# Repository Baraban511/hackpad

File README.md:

# baraboard
### A complete board designed by me for me with help of many !

# BOM:

    [ ] 1x PCB
    [ ] 12x Cherry MX switches
    [ ] 1x EC11 Encoder
    [ ] 12x WS2812B LEDs

### If possible, I would like the plate in acrylic and the pcb and the case in black. If it's not possible, feel free to choose the best option.

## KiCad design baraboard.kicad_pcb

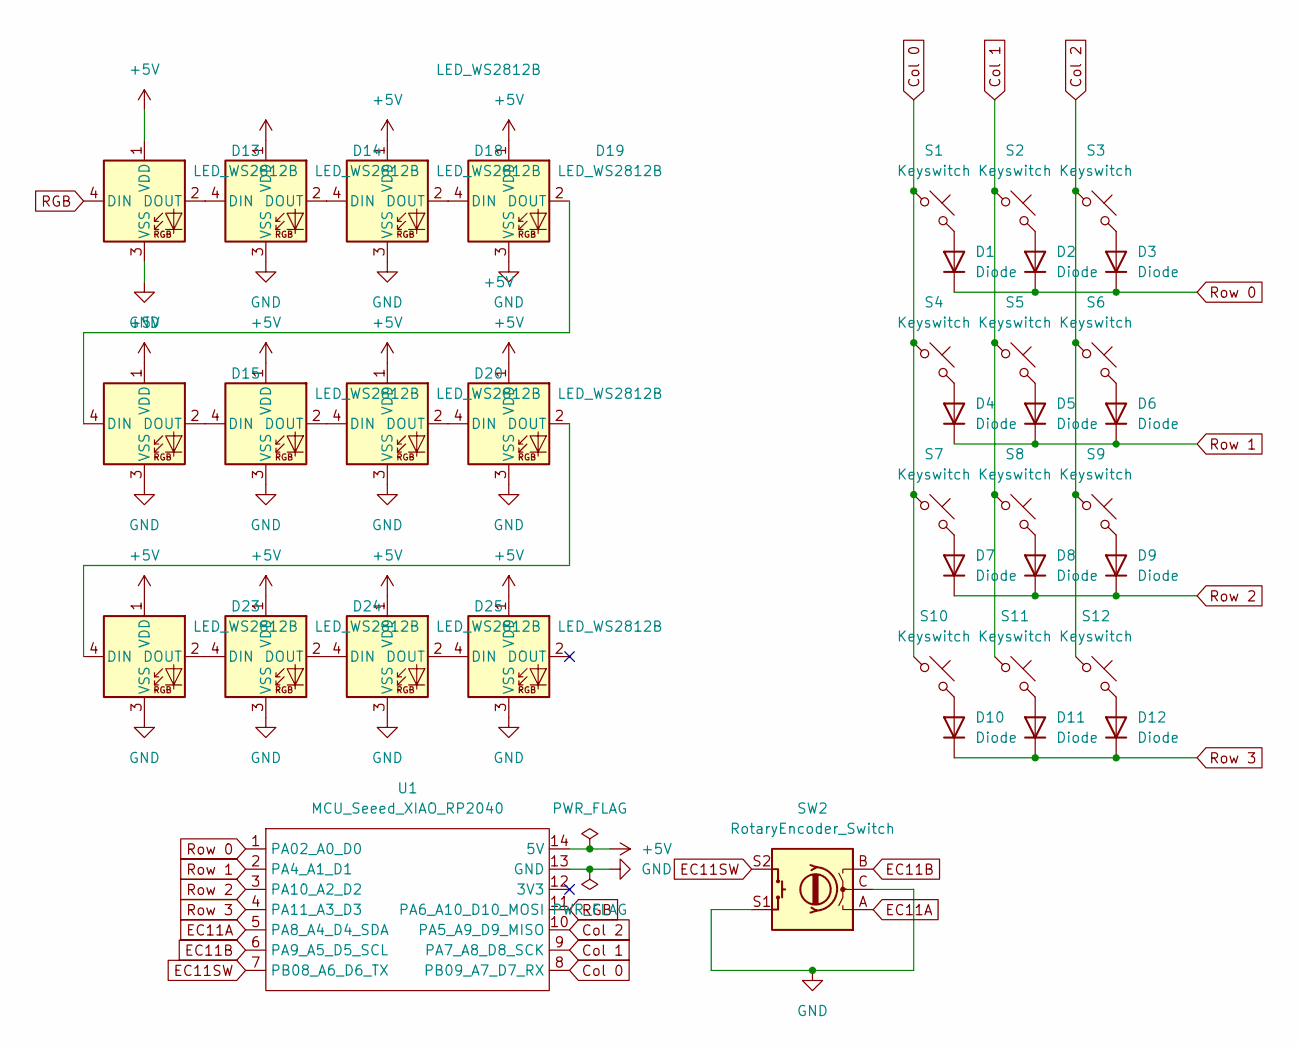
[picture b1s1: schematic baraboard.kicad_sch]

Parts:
D1, D2, D3, D4, D5, D6, D7, D8, D9, D10, D11, D12: Diode; Diode_DO-35
D13, D14, D15, D16, D18, D19, D20, D21, D23, D24, D25, D26: LED_WS2812B; LED_SK6812MINI
S1, S2, S3, S4, S5, S6, S7, S8, S9, S10, S12: Keyswitch; Hotswap_MX_Plated_1.00u
S11: Keyswitch; Hotswap_MX_Plated_2.00u
SW2: RotaryEncoder_Switch; RotaryEncoder_Alps_EC11E-Switch_Vertical_H20mm
U1: MCU_Seeed_XIAO_RP2040; Seeed_XIAO_RP2040

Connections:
+5V: D13.1 (VDD), D14.1 (VDD), D15.1 (VDD), D16.1 (VDD), D18.1 (VDD), D19.1 (VDD), D20.1 (VDD), D21.1 (VDD), D23.1 (VDD), D24.1 (VDD), D25.1 (VDD), D26.1 (VDD), U1.14 (5V)
Col 0: S1.1, S4.1, S7.1, S10.1, U1.8 (PB09_A7_D7_RX)
Col 1: S2.1, S5.1, S8.1, S11.1, U1.9 (PA7_A8_D8_SCK)
Col 2: S3.1, S6.1, S9.1, S12.1, U1.10 (PA5_A9_D9_MISO)
EC11A: SW2.A, U1.5 (PA8_A4_D4_SDA)
EC11B: SW2.B, U1.6 (PA9_A5_D5_SCL)
EC11SW: SW2.S2, U1.7 (PB08_A6_D6_TX)
GND: D13.3 (VSS), D14.3 (VSS), D15.3 (VSS), D16.3 (VSS), D18.3 (VSS), D19.3 (VSS), D20.3 (VSS), D21.3 (VSS), D23.3 (VSS), D24.3 (VSS), D25.3 (VSS), D26.3 (VSS), SW2.C, SW2.S1, U1.13 (GND)
unnamed: D1.2 (A), S1.2
unnamed: D2.2 (A), S2.2
unnamed: D3.2 (A), S3.2
unnamed: D4.2 (A), S4.2
unnamed: D5.2 (A), S5.2
unnamed: D6.2 (A), S6.2
unnamed: D7.2 (A), S7.2
unnamed: D8.2 (A), S8.2
unnamed: D9.2 (A), S9.2
unnamed: D10.2 (A), S10.2
unnamed: D11.2 (A), S11.2
unnamed: D12.2 (A), S12.2
unnamed: D13.2 (DOUT), D14.4 (DIN)
unnamed: D14.2 (DOUT), D15.4 (DIN)
unnamed: D15.2 (DOUT), D19.4 (DIN)
unnamed: D16.4 (DIN), D18.2 (DOUT)
unnamed: D16.2 (DOUT), D20.4 (DIN)
unnamed: D18.4 (DIN), D19.2 (DOUT)
unnamed: D20.2 (DOUT), D21.4 (DIN)
unnamed: D21.2 (DOUT), D23.4 (DIN)
unnamed: D23.2 (DOUT), D24.4 (DIN)
unnamed: D24.2 (DOUT), D25.4 (DIN)
unnamed: D25.2 (DOUT), D26.4 (DIN)
RGB: D13.4 (DIN), U1.11 (PA6_A10_D10_MOSI)
Row 0: D1.1 (K), D2.1 (K), D3.1 (K), U1.1 (PA02_A0_D0)
Row 1: D4.1 (K), D5.1 (K), D6.1 (K), U1.2 (PA4_A1_D1)
Row 2: D7.1 (K), D8.1 (K), D9.1 (K), U1.3 (PA10_A2_D2)
Row 3: D10.1 (K), D11.1 (K), D12.1 (K), U1.4 (PA11_A3_D3)

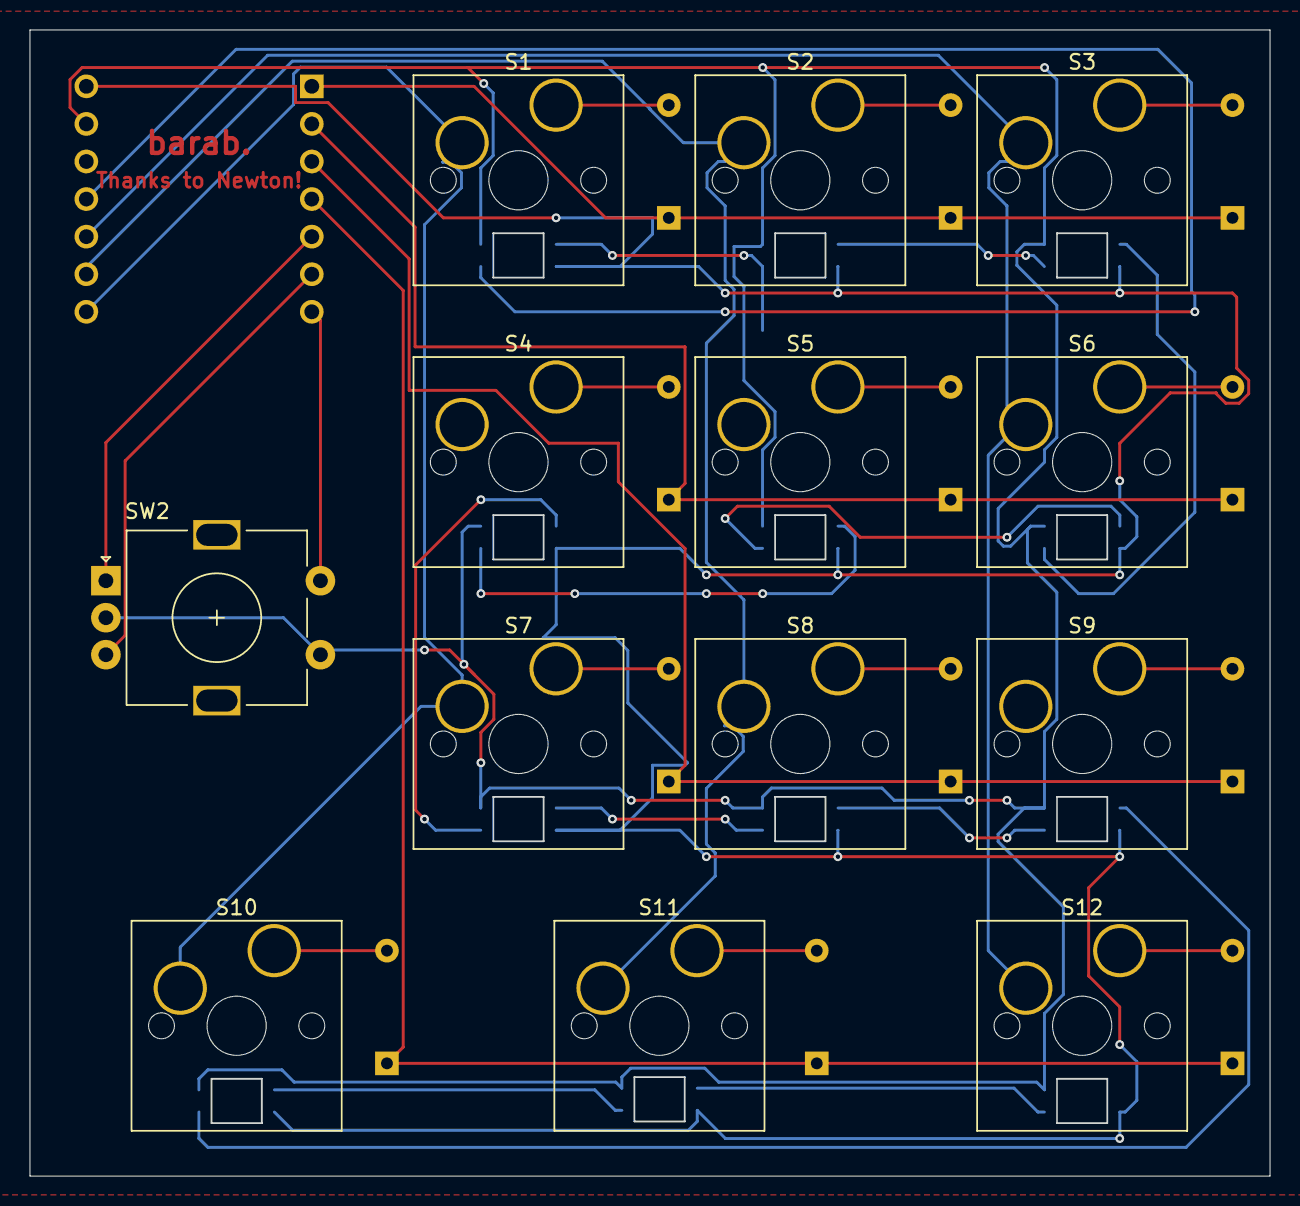
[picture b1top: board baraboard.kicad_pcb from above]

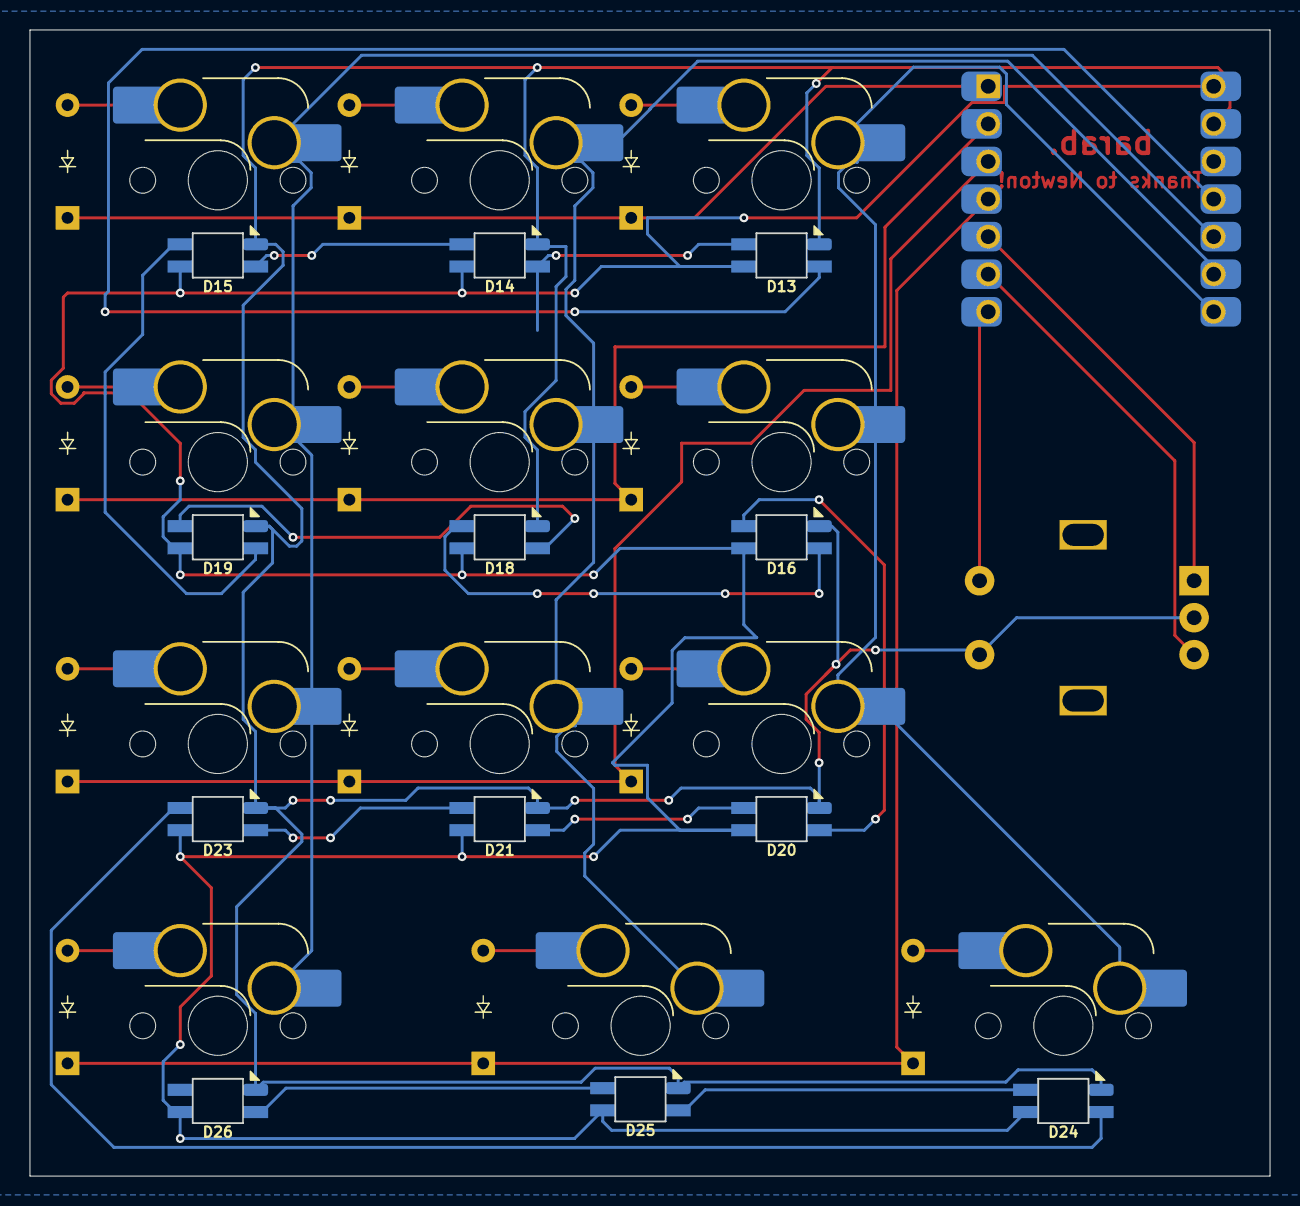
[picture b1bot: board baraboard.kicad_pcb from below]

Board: 2 copper layers, 83.8 x 77.5 mm, 38 parts (13 on the bottom side), 36 nets.

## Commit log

2024-09-20 schema is done, pcb on the way
2024-09-21 PCB done, case coming
2024-09-24 PCB complete, case start
2024-10-08 baraboard is ready to ship !
2024-10-12 Final case design
2024-10-13 Updating firmware
